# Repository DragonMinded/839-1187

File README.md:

A reproduction of the SEGA 839-1187 analog amplifier board, useable in several games. This project is already shared on OSH Park here: https://oshpark.com/shared_projects/Y6ouPNpT but you can also use the KiCad project to generate gerbers for your favorite PCB fabricator. Also, see `839-1187 clone.txt` for BOM and links for purchasing, and see the `bom/` directory for an interactive BOM page that makes assembly easier. Enjoy and happy Monkey Balling!

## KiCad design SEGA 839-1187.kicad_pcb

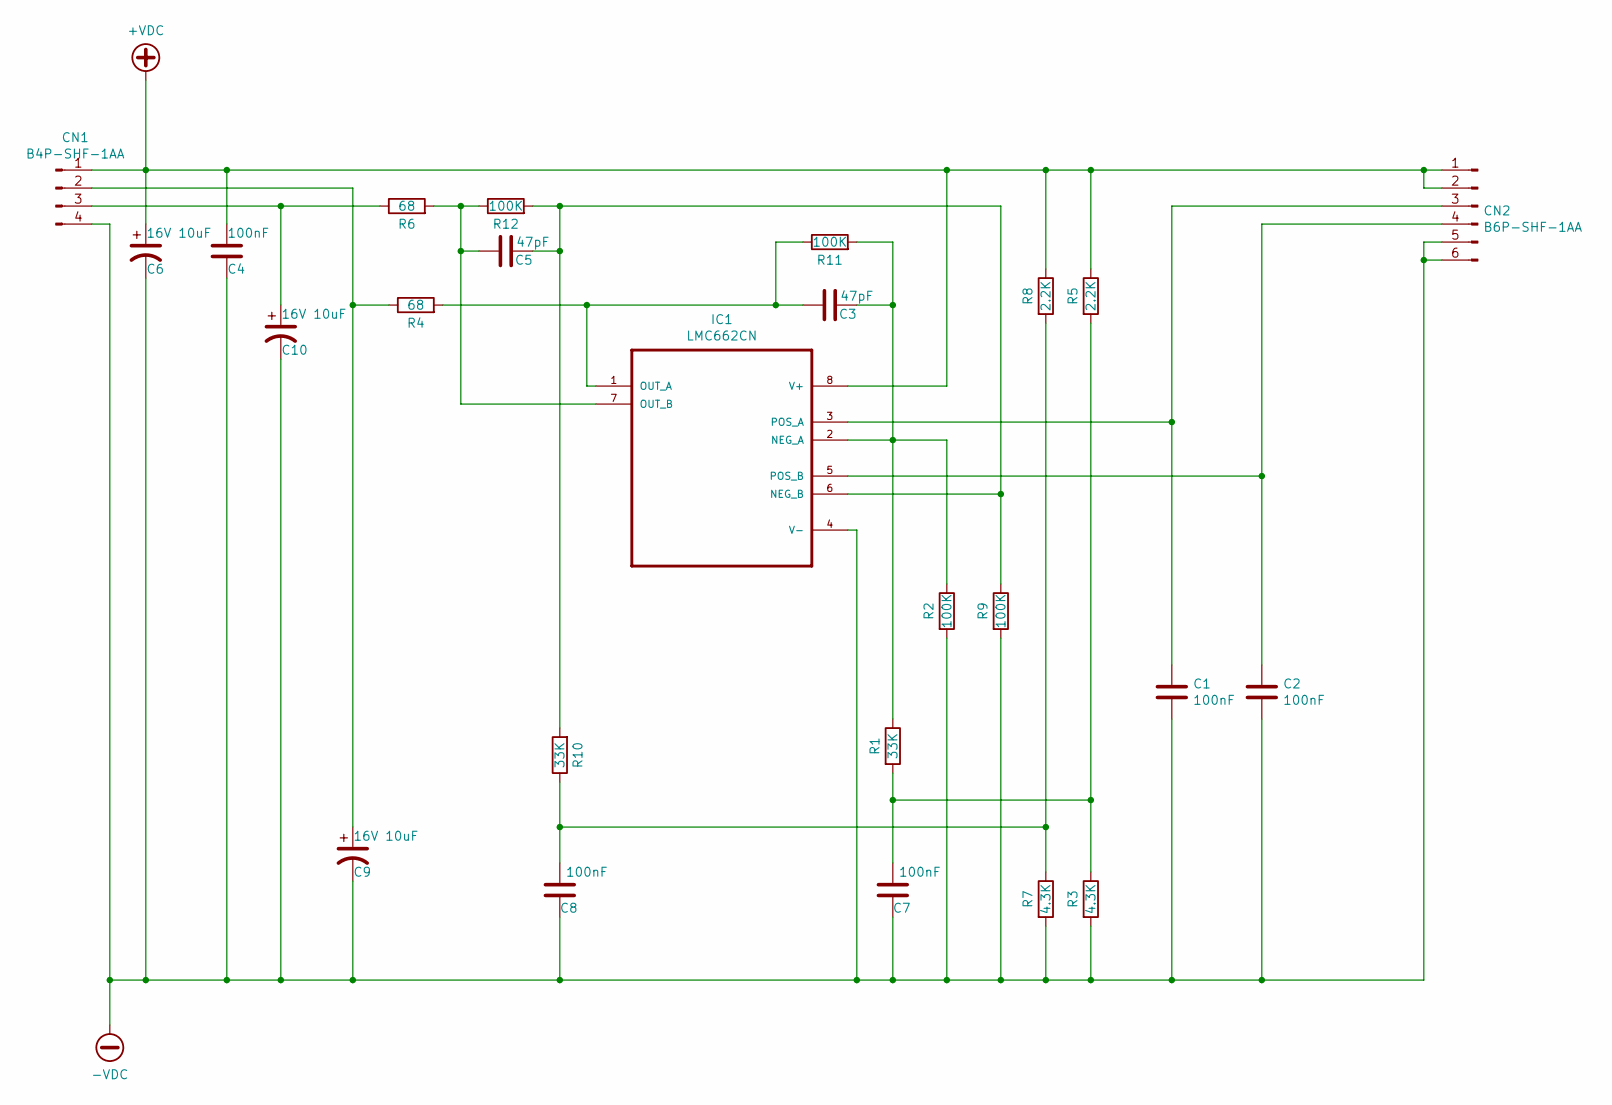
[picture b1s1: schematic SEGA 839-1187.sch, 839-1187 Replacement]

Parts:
C1, C2, C4, C7, C8: 100nF; C_Disc_D4.3mm_W1.9mm_P5.00mm
C3, C5: 47pF; C_Disc_D4.3mm_W1.9mm_P5.00mm
C6, C9, C10: 16V 10uF; CP_Radial_D6.3mm_P2.50mm
CN1: B4P-SHF-1AA; JST_EH_B4B-EH-A_1x04_P2.50mm_Vertical
CN2: B6P-SHF-1AA; JST_EH_B6B-EH-A_1x06_P2.50mm_Vertical
IC1: LMC662CN; DIP254P762X508-8
R1, R10: 33K; R_Axial_DIN0204_L3.6mm_D1.6mm_P7.62mm_Horizontal
R2, R9, R11, R12: 100K; R_Axial_DIN0204_L3.6mm_D1.6mm_P7.62mm_Horizontal
R3, R7: 4.3K; R_Axial_DIN0204_L3.6mm_D1.6mm_P7.62mm_Horizontal
R4, R6: 68; R_Axial_DIN0204_L3.6mm_D1.6mm_P7.62mm_Horizontal
R5, R8: 2.2K; R_Axial_DIN0204_L3.6mm_D1.6mm_P7.62mm_Horizontal

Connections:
+VDC: C4.1, C6.1, CN1.1, CN2.1, CN2.2, IC1.8 (V+), R5.1, R8.1
-VDC: C1.2, C2.2, C4.2, C6.2, C7.1, C8.1, C9.2, C10.2, CN1.4, CN2.5, CN2.6, IC1.4 (V-), R2.2, R3.2, R7.2, R9.2
unnamed: C1.1, CN2.3, IC1.3 (POS_A)
unnamed: C2.1, CN2.4, IC1.5 (POS_B)
unnamed: C3.1, IC1.1 (OUT_A), R4.2, R11.1
unnamed: C3.2, IC1.2 (NEG_A), R1.1, R2.1, R11.2
unnamed: C5.1, IC1.7 (OUT_B), R6.2, R12.1
unnamed: C5.2, IC1.6 (NEG_B), R9.1, R10.2, R12.2
unnamed: C7.2, R1.2, R3.1, R5.2
unnamed: C8.2, R7.1, R8.2, R10.1
unnamed: C9.1, CN1.2, R4.1
unnamed: C10.1, CN1.3, R6.1

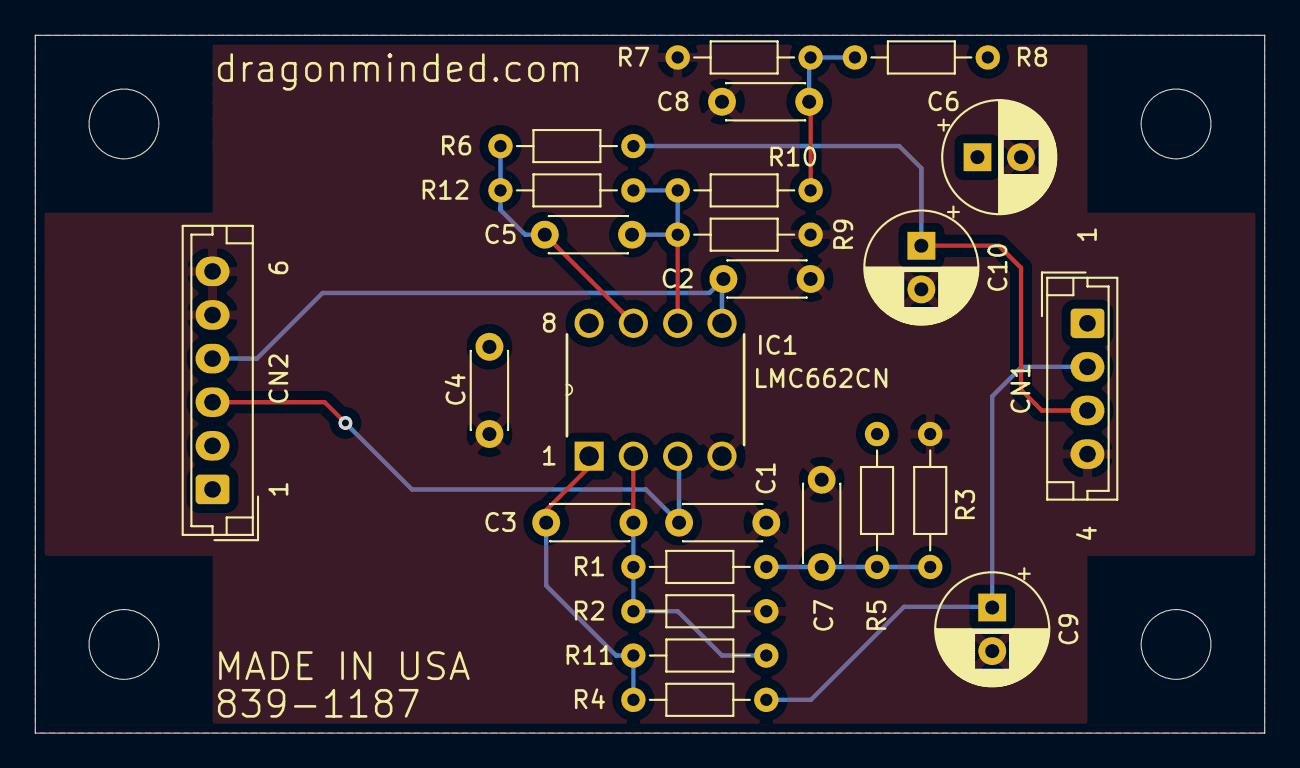
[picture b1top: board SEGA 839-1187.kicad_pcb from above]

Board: 2 copper layers, 70.5 x 40.0 mm, 25 parts (0 on the bottom side), 12 nets.

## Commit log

2021-12-20 Initial commit of files.
